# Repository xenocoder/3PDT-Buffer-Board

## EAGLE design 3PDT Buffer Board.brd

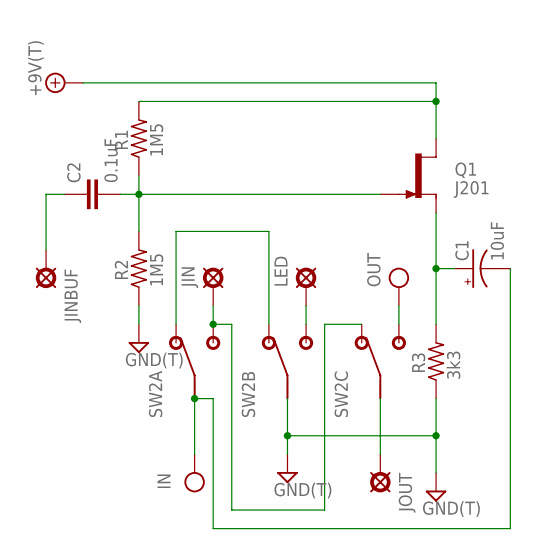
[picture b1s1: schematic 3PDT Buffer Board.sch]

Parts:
+9V: +9V(T); SQUARE
C1: 10uF; 050_020_1
C2: 0.1uF; 080X050
G: GND(T); SQUARE
IN: IN(T); SQUARE
JIG: GND(T); SQUARE
JIN: PAD; SQUARE
JINBUF: PAD; SQUARE
JOG: GND(T); SQUARE
JOUT: PAD; SQUARE
LED: PAD; SQUARE
OUT: OUT(T); SQUARE
Q1: J201; TO92-
R1, R2: 1M5; R0207/3
R3: 3k3; R0207/3
SW2: 3PDT

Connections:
+9V: +9V.1, Q1.3 (D), R1.2
GND: G.1, JIG.1, JOG.1, R2.1, R3.1, SW2.B2 (2)
IN: C1.-, IN.1, SW2.A2 (2)
unnamed: LED.1, SW2.B3 (3)
unnamed: JOUT.1, SW2.C2 (2)
unnamed: SW2.A1 (1), SW2.B1 (1)
unnamed: JIN.1, SW2.A3 (3), SW2.C1 (1)
unnamed: C2.2, Q1.1 (G), R1.1, R2.2
unnamed: C2.1, JINBUF.1
unnamed: C1.+, Q1.2 (S), R3.2
OUT: OUT.1, SW2.C3 (3)

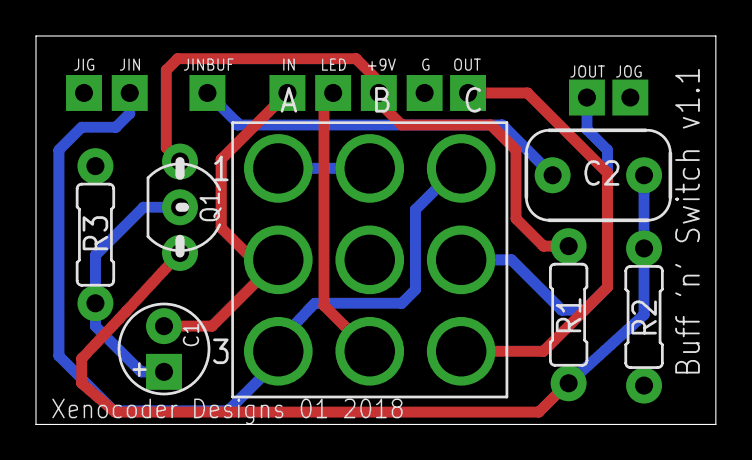
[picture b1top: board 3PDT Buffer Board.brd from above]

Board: 2 copper layers, 37.8 x 21.6 mm, 17 parts (0 on the bottom side), 11 nets.

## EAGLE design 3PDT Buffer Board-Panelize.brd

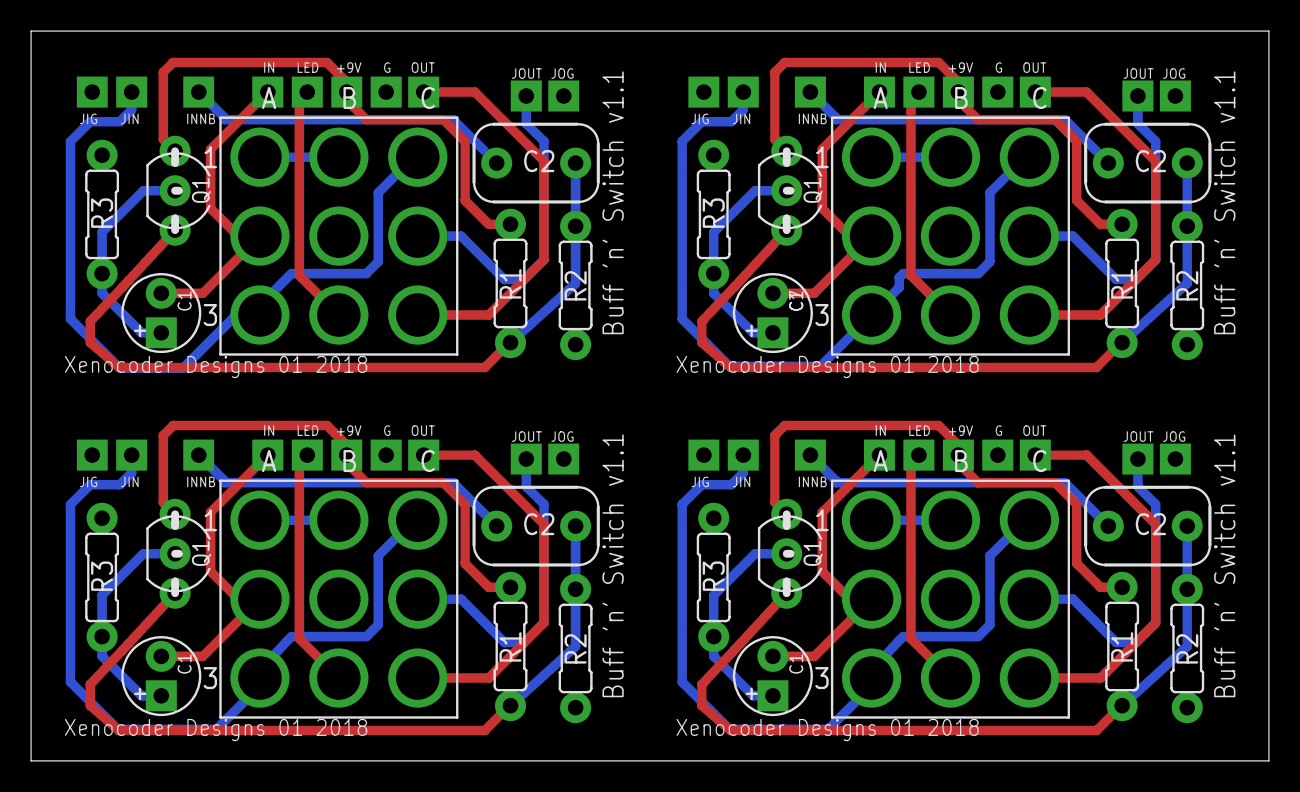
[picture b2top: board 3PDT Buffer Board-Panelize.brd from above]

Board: 2 copper layers, 79.7 x 47.0 mm, 68 parts (0 on the bottom side), 44 nets.

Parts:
+9V, +9V1, +9V2, +9V3: +9V(T); SQUARE
C1, C3, C5, C7: 10uF; 050_020_1
C2, C4, C6, C8: 0.1uF; 080X050
G, G1, G2, G3: GND(T); SQUARE
IN, IN1, IN2, IN3: IN(T); SQUARE
INNB, INNB1, INNB2, INNB3: SQUARE
JIG, JIG1, JIG2, JIG3: GND(T); SQUARE
JIN, JIN1, JIN2, JIN3: SQUARE
JOG, JOG1, JOG2, JOG3: GND(T); SQUARE
JOUT, JOUT1, JOUT2, JOUT3: SQUARE
LED, LED1, LED2, LED3: SQUARE
OUT, OUT1, OUT2, OUT3: OUT(T); SQUARE
Q1, Q2, Q3, Q4: J201; TO92-
R1, R2, R4, R5, R7, R8, R10, R11: 1M5; R0207/3
R3, R6, R9, R12: 3k3; R0207/3
SW1, SW2, SW3, SW4: 3PDT

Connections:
+9V: +9V.1, Q1.3, R1.2
+9V1: +9V1.1, Q2.3, R4.2
+9V2: +9V2.1, Q3.3, R7.2
+9V3: +9V3.1, Q4.3, R10.2
GND: G.1, JIG.1, JOG.1, R2.1, R3.1, SW2.B2
GND1: G1.1, JIG1.1, JOG1.1, R5.1, R6.1, SW1.B2
GND2: G2.1, JIG2.1, JOG2.1, R8.1, R9.1, SW3.B2
GND3: G3.1, JIG3.1, JOG3.1, R11.1, R12.1, SW4.B2
IN: C1.-, IN.1, SW2.A2
IN1: C3.-, IN1.1, SW1.A2
IN2: C5.-, IN2.1, SW3.A2
IN3: C7.-, IN3.1, SW4.A2
unnamed: LED.1, SW2.B3
unnamed: JOUT.1, SW2.C2
unnamed: SW2.A1, SW2.B1
unnamed: JIN.1, SW2.A3, SW2.C1
unnamed: C2.2, Q1.1, R1.1, R2.2
unnamed: C2.1, INNB.1
unnamed: C1.+, Q1.2, R3.2
unnamed: LED1.1, SW1.B3
unnamed: JOUT1.1, SW1.C2
unnamed: SW1.A1, SW1.B1
unnamed: JIN1.1, SW1.A3, SW1.C1
unnamed: C4.2, Q2.1, R4.1, R5.2
unnamed: C3.+, Q2.2, R6.2
unnamed: C4.1, INNB1.1
unnamed: LED2.1, SW3.B3
unnamed: JOUT2.1, SW3.C2
unnamed: SW3.A1, SW3.B1
unnamed: JIN2.1, SW3.A3, SW3.C1
unnamed: C6.2, Q3.1, R7.1, R8.2
unnamed: C5.+, Q3.2, R9.2
unnamed: C6.1, INNB2.1
unnamed: LED3.1, SW4.B3
unnamed: JOUT3.1, SW4.C2
unnamed: SW4.A1, SW4.B1
unnamed: JIN3.1, SW4.A3, SW4.C1
unnamed: C8.2, Q4.1, R10.1, R11.2
unnamed: C7.+, Q4.2, R12.2
unnamed: C8.1, INNB3.1
OUT: OUT.1, SW2.C3
OUT1: OUT1.1, SW1.C3
OUT2: OUT2.1, SW3.C3
OUT3: OUT3.1, SW4.C3

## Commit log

2018-08-24 First Version of buffer board for Git
2018-09-06 Added Partslist
2018-09-30 Made first panelized board
2018-09-30 Added PCB image
